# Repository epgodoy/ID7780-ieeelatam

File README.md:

# ID7780-ieeelatam
Arquivos e dados adicionais relacionados ao artigo ID7780 - IEEE Latin America Transactions

Este repositório contém arquivos e dados adicionais referentes ao artigo "Advanced Metering Infrastructure for Industrial Natural Gas Smart Management" (ID7780) do IEEE Latin America Transactions:         
- https://latamt.ieeer9.org/index.php/transactions/article/view/7780              
- https://ieeexplore.ieee.org/document/10255447      

A arquitetura da AMI para gestão inteligente de gás natural em clientes industriais mostrada na Fig. 1 do artigo é composta de quatro elementos: corretor de volume de gás PTZ, hardware eletrônico de aquisição de dados e comunicação, servidor de rede LoRaWAN e plataforma de IoT da ProIoT.

Sobre o módulo desenvolvido - hardware eletrônico de aquisição de dados e comunicação, disponibiliza-se:
- código fonte compilado para o microcontrolador ESP32 da fabricante Espressif
- esquemático do projeto eletrônico
- projeto (layout) da placa de circuito impresso
- projeto para impressora 3D do invólucro

A licença é GPL-3.0. Em caso de uso, cite nosso trabalho.     
E. Camoleze de Araújo, N. C. de Almeida and E. P. Godoy, "Advanced Metering Infrastructure for Industrial Natural Gas Smart Management," in IEEE Latin America Transactions, vol. 21, no. 10, pp. 1081-1087, Oct. 2023, doi: 10.1109/TLA.2023.10255447

Abstract: One of the challenges within the utilities sector is the development of robust, scalable and low-cost methods for the remote management of customers usage and billing. Considering the advances related to the Internet of Things (IoT), an Advanced Metering Infrastructure (AMI) is the basis for utilities smart management. This AMI bring together the automation of remote metering and communication infrastructures with the processing and analysis of distributed data using advanced techniques and cloud computing. This paper presents the development of an AMI for the smart management of natural gas industrial customers using IoT. The AMI architecture is based on the LoRaWAN communication for remote metering and a cloud-based smart management system including supervisory control, continuous monitoring, anomalies detection and alarm notification. Experimental results shown the LoRaWAN fulfilled the communication requirements for industrial natural gas metering and the smart management system can analyze historical data and detect anomalies in gas consumption.

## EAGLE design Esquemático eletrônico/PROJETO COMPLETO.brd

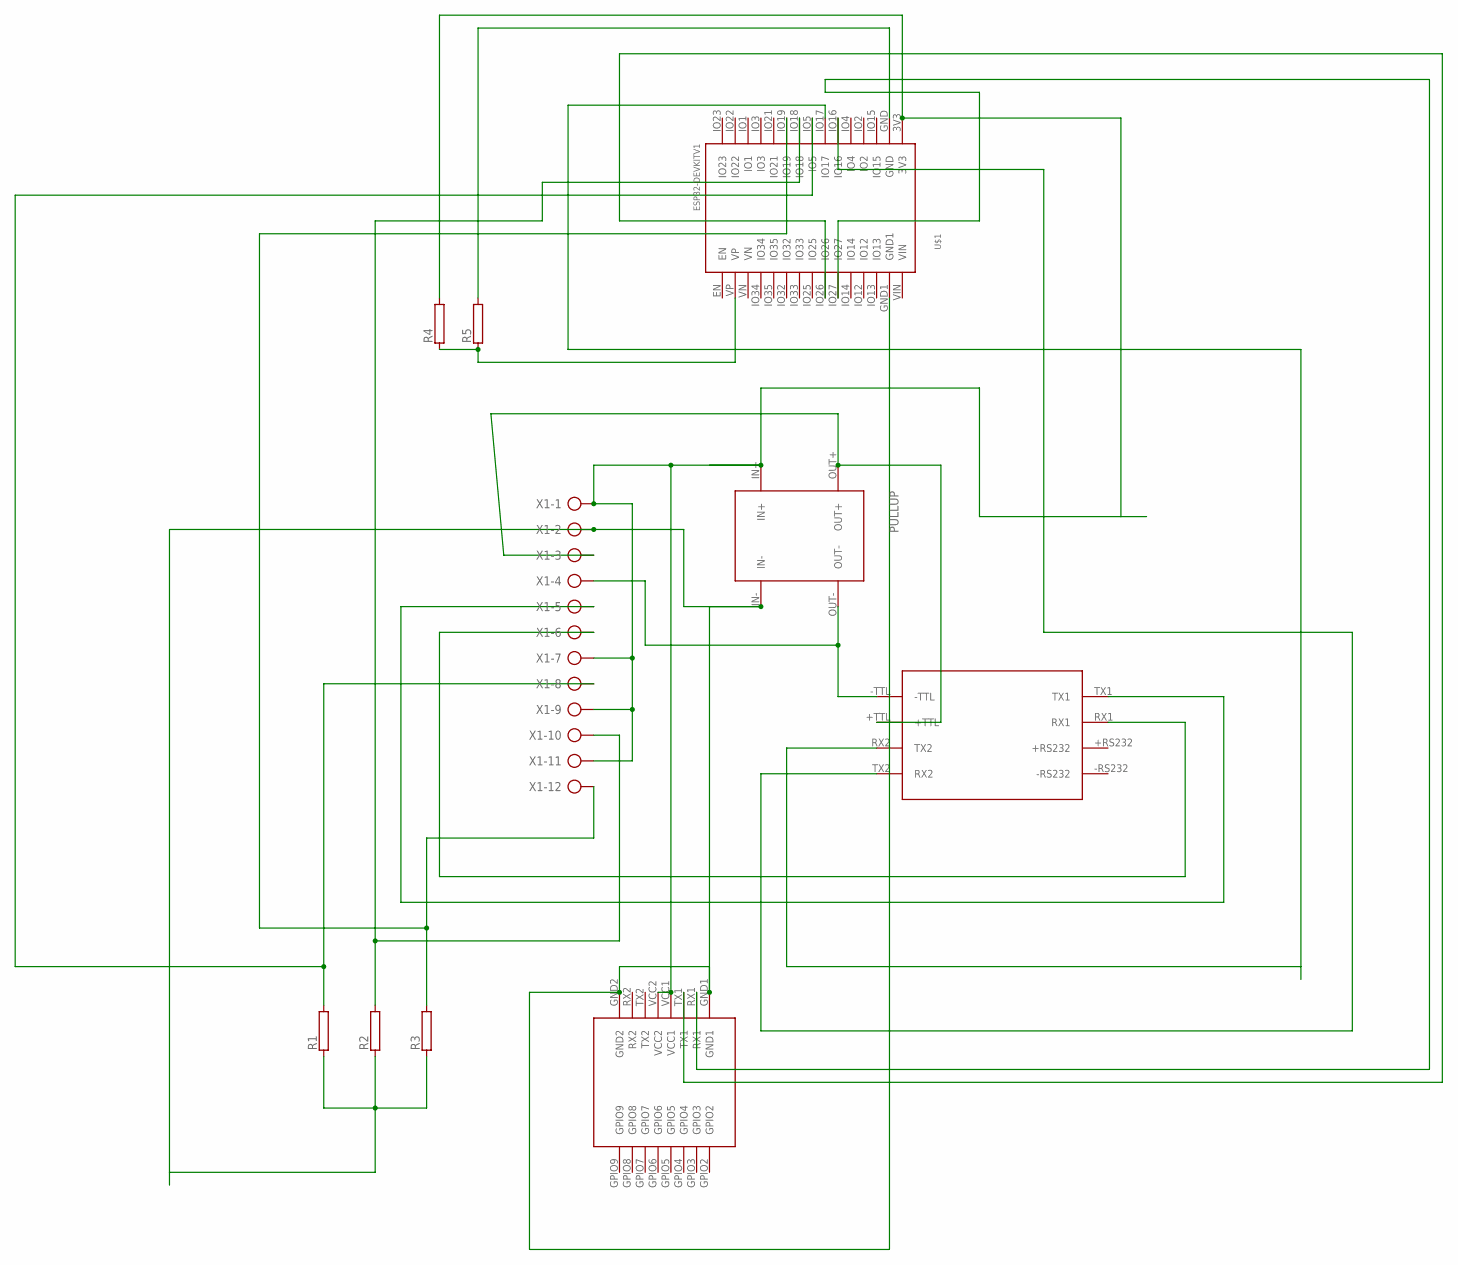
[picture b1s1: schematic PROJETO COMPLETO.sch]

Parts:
R1, R2, R3, R4, R5: RAC01; AC01
U$1: ESP32DEVKITV1; ESP32-DEVKITV1
U$2: RADIOENGE
U$3: MAX3232
U$4: PULLUP
X1: AK500/12-H

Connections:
unnamed: U$1.IO17, U$3.RX2 (TX2)
unnamed: U$1.IO16, U$3.TX2 (RX2)
unnamed: U$3.+TTL, U$4.OUT+, X1.3
unnamed: U$3.-TTL, U$4.OUT-, X1.4
unnamed: U$3.TX1, X1.5
unnamed: U$3.RX1, X1.6
unnamed: R5.2, U$1.GND
unnamed: R4.1, R5.1, U$1.VP
unnamed: U$1.IO27, U$2.RX1
unnamed: U$1.IO26, U$2.TX1
unnamed: R3.2, U$1.IO19, X1.12
unnamed: R2.2, U$1.IO18, X1.10
unnamed: R1.2, U$1.IO5, X1.8
unnamed: R1.1, R2.1, R3.1, U$1.GND1, U$2.GND1, U$2.GND2, U$4.IN-, X1.2
unnamed: R4.2, U$1.3V3, U$2.VCC1, U$2.VCC2, U$4.IN+, X1.1, X1.7, X1.9, X1.11

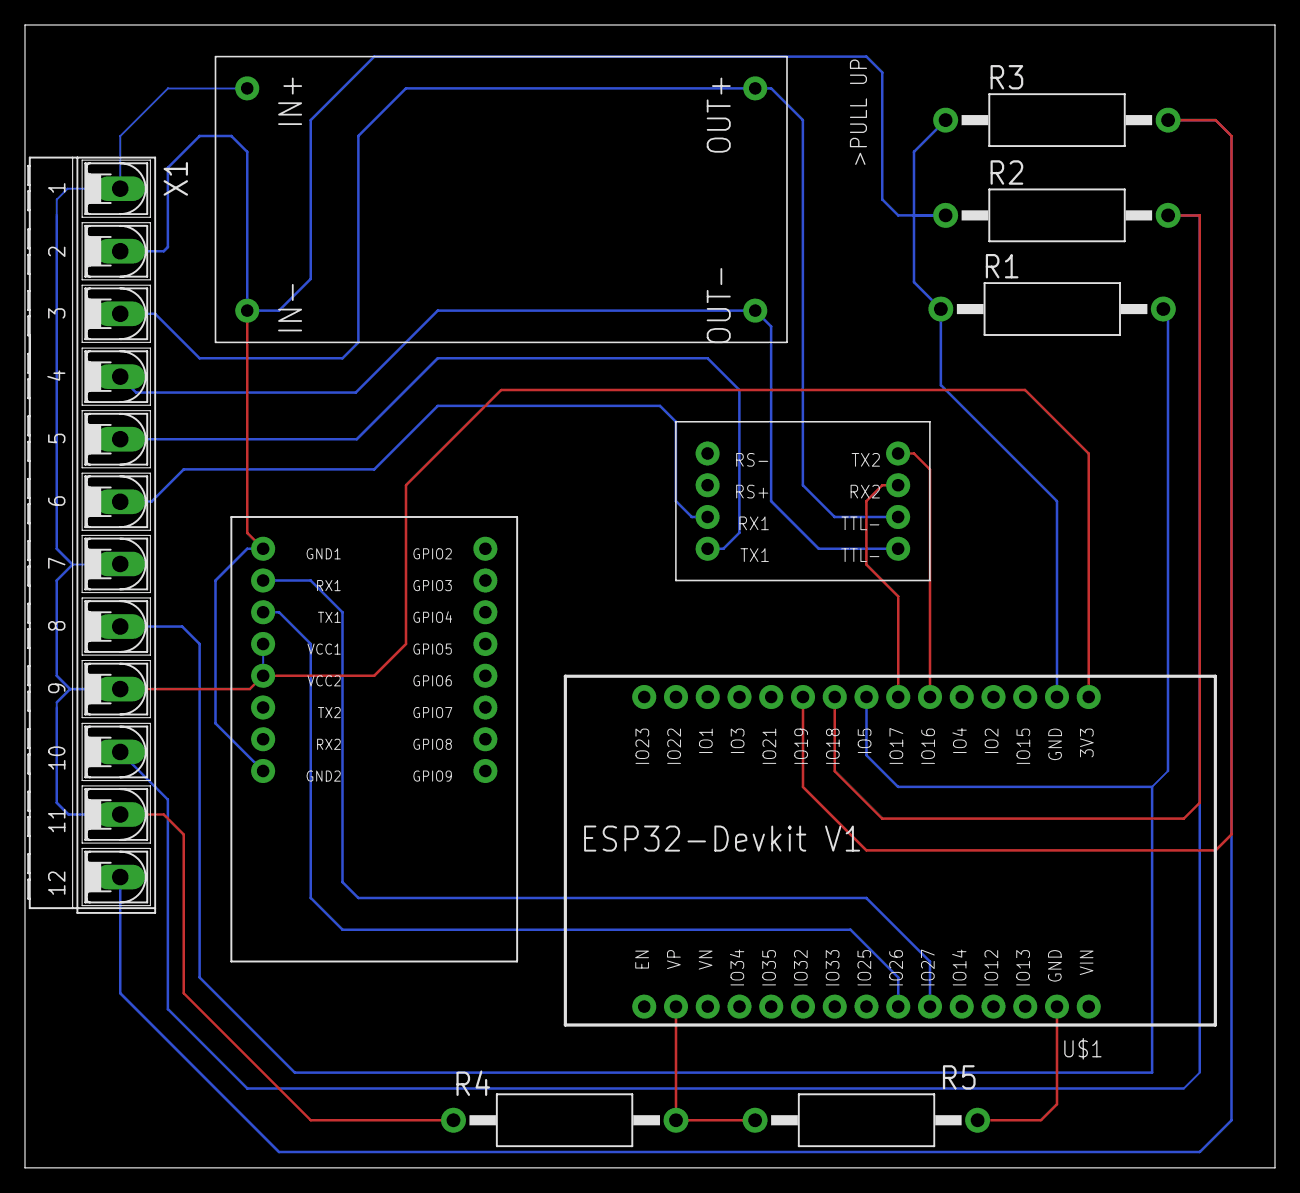
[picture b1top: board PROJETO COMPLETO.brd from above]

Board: 2 copper layers, 100.0 x 91.4 mm, 10 parts (0 on the bottom side), 15 nets.
